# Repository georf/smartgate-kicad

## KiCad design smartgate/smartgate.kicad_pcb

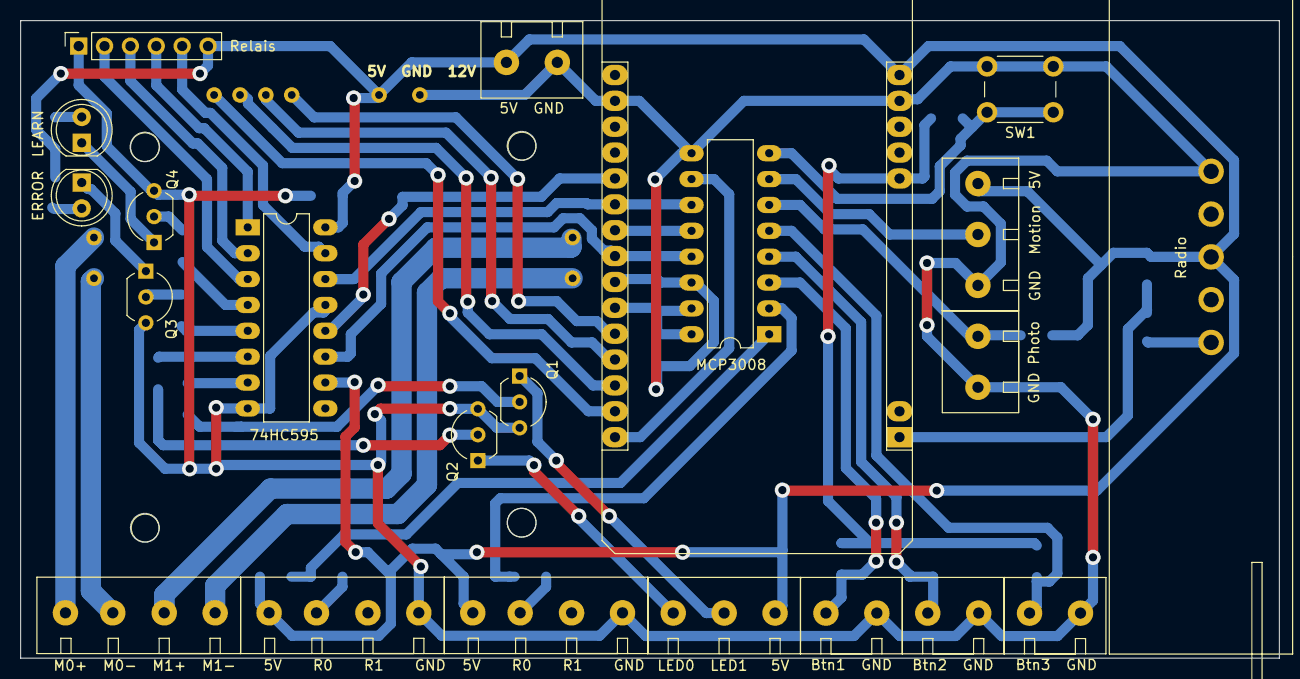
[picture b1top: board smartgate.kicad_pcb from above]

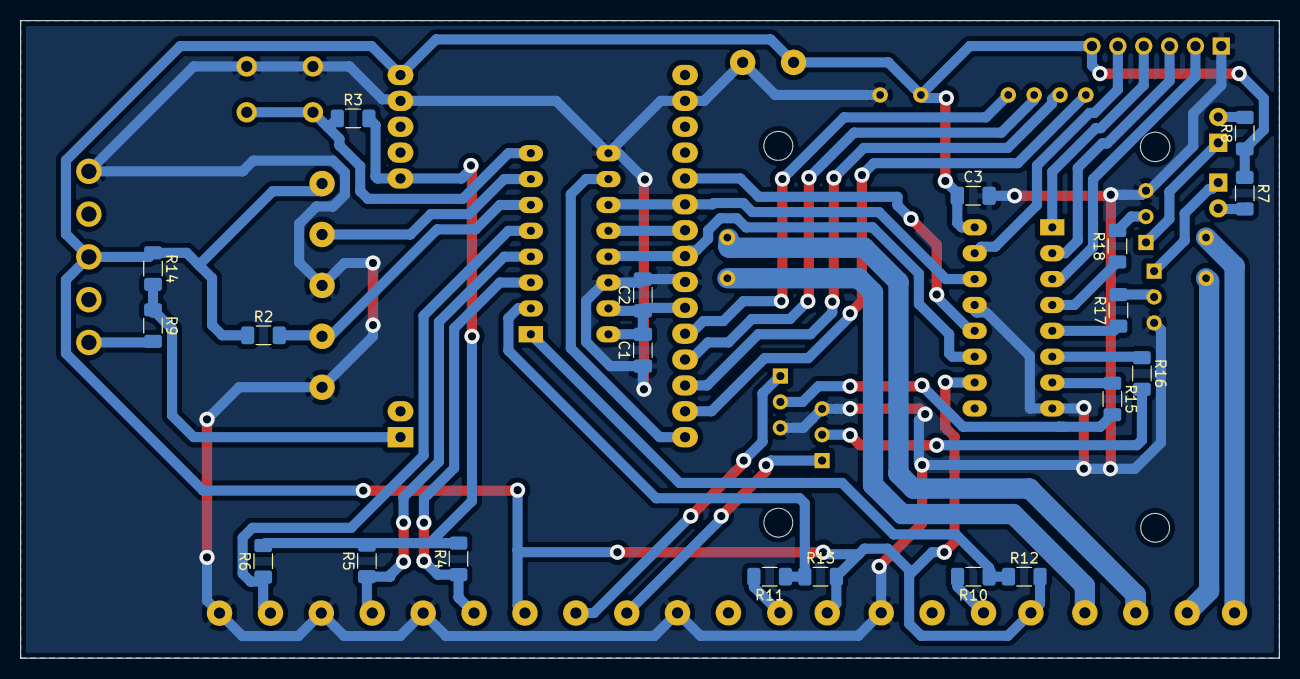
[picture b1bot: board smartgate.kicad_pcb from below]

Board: 2 copper layers, 123.6 x 62.6 mm, 43 parts (20 on the bottom side), 46 nets.

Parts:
5V    R0    R1    GND : Conn_M0_GPIO; Connector_4xPin
5V    R0    R1    GND #2: Conn_M1_GPIO; Connector_4xPin
5V  GND: Conn_Voltage5_Input; Connector 2xPin
74HC595: 74HC595; DIP-16_W7.62mm_LongPads
Btn1  GND: Conn_Btn1; Connector 2xPin
Btn2  GND: Conn_Btn2; Connector 2xPin
Btn3  GND: Conn_Btn3; Connector 2xPin
C1, C2, C3: 1uF; C_1206_3216Metric_Pad1.33x1.80mm_HandSolder
ERROR: LED_Status0; LED_D5.0mm
GND  Motion  5V: Conn_Motion; Connector 3xPin
GND Photo: R_PHOTO1; Connector 2xPin
LEARN: LED_Status1; LED_D5.0mm
LED0  LED1   5V: Conn_Warn_LED; Connector 3xPin
M0+  M0-  M1+  M1-: Conn_Motor; Connector_4xPin
MCP3008: MCP3008; DIP-16_W7.62mm_LongPads
Q1, Q2, Q3, Q4: BC547; TO-92_Inline_Wide
R2: 1k; R_1206_3216Metric_Pad1.30x1.75mm_HandSolder
R3, R4, R5, R6, R9, R10, R11, R12, R13, R14: 12k; R_1206_3216Metric_Pad1.30x1.75mm_HandSolder
R7, R8: 100; R_1206_3216Metric_Pad1.30x1.75mm_HandSolder
R15, R16, R17, R18: 2k2; R_1206_3216Metric_Pad1.30x1.75mm_HandSolder
Radio: Conn_Radio; Radio-Transmitter
Relais: Conn_Relais; PinSocket_1x06_P2.54mm_Vertical
SW1: Btn0; SW_PUSH_6mm_H4.3mm
U2: NodeMCU_Amica_R2_weniger_pins; node_MCU_ESP8266_weniger_pins_longpad
U5: H-Bridge

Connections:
+3V3: C1.2, C2.1, MCP3008.15, MCP3008.16, R3.2, R4.2, R5.2, R6.2, U2.11, U2.25
+5V: 5V R0 R1 GND.4, 5V R0 R1 GND #2.4, 5V GND.1, 74HC595.10, 74HC595.16, C3.1, GND Motion 5V.1, LED0 LED1 5V.1, R2.1, R7.1, R8.1, R12.2, R13.2, R14.1, Radio.3, Relais.6, U2.15, U5.5
Btn0: MCP3008.8, R3.1, SW1.1
Btn1: Btn1 GND.2, MCP3008.3, R4.1
Btn2: Btn2 GND.2, MCP3008.4, R5.1
Btn3: Btn3 GND.2, MCP3008.5, R6.1
GND: 5V R0 R1 GND.1, 5V R0 R1 GND #2.1, 5V GND.2, 74HC595.8, 74HC595.13, Btn1 GND.1, Btn2 GND.1, Btn3 GND.1, C1.1, C2.2, C3.2, GND Motion 5V.3, GND Photo.2, MCP3008.9, MCP3008.14, Q1.3, Q2.3, Q3.3, Q4.3, Radio.1, Relais.1, SW1.2, U2.14, U2.17, U2.24, U5.4
M0_0: U2.26, U5.6
M0_1: U2.27, U5.7
M0_Speed: MCP3008.1, R10.1, R12.1
M1_0: U2.28, U5.8
M1_1: U2.29, U5.9
M1_Speed: MCP3008.2, R11.1, R13.1
MISO: MCP3008.12, U2.22
MOSI: 74HC595.14, MCP3008.11, U2.21
Motion: GND Motion 5V.2, MCP3008.7
unnamed: ERROR.1, Q3.1
unnamed: ERROR.2, R7.2
unnamed: LEARN.1, Q4.1
unnamed: LEARN.2, R8.2
unnamed: 5V R0 R1 GND.3, R10.2
unnamed: 5V R0 R1 GND #2.3, R11.2
unnamed: LED0 LED1 5V.2, Q1.1
unnamed: LED0 LED1 5V.3, Q2.1
unnamed: 74HC595.3, Relais.2
unnamed: 74HC595.2, Relais.3
unnamed: 74HC595.1, Relais.4
unnamed: 74HC595.15, Relais.5
unnamed: M0+ M0- M1+ M1-.1, U5.1
unnamed: M0+ M0- M1+ M1-.2, U5.2
unnamed: M0+ M0- M1+ M1-.3, U5.11
unnamed: M0+ M0- M1+ M1-.4, U5.10
unnamed: R9.2, Radio.5
unnamed: Q1.2, R15.2
unnamed: Q2.2, R16.2
unnamed: Q3.2, R17.2
unnamed: Q4.2, R18.2
unnamed: 74HC595.7, R15.1
unnamed: 74HC595.6, R16.1
unnamed: 74HC595.5, R17.1
unnamed: 74HC595.4, R18.1
Photo: GND Photo.1, MCP3008.6, R2.2
Radio: R9.1, R14.2, U2.1
SPI_595: 74HC595.12, U2.20
SPI_3008: MCP3008.10, U2.30
SPI_CLK: 74HC595.11, MCP3008.13, U2.23

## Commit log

2023-02-04 version1
